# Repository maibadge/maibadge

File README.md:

# MaiBadge

MaiBadge PCB designs, artwork, and firmware.

The maintained CircuitPython firmware for both the bear-shaped and
machine-shaped PCBs is in
[`code/circuitpython-full-slop-port`](code/circuitpython-full-slop-port).
Choose `bear_v1` or `machine_v2` in that directory's `settings.toml` before
uploading. See the
[`manual upload guide`](code/circuitpython-full-slop-port/MANUAL_UPLOAD.md) for
complete installation instructions.

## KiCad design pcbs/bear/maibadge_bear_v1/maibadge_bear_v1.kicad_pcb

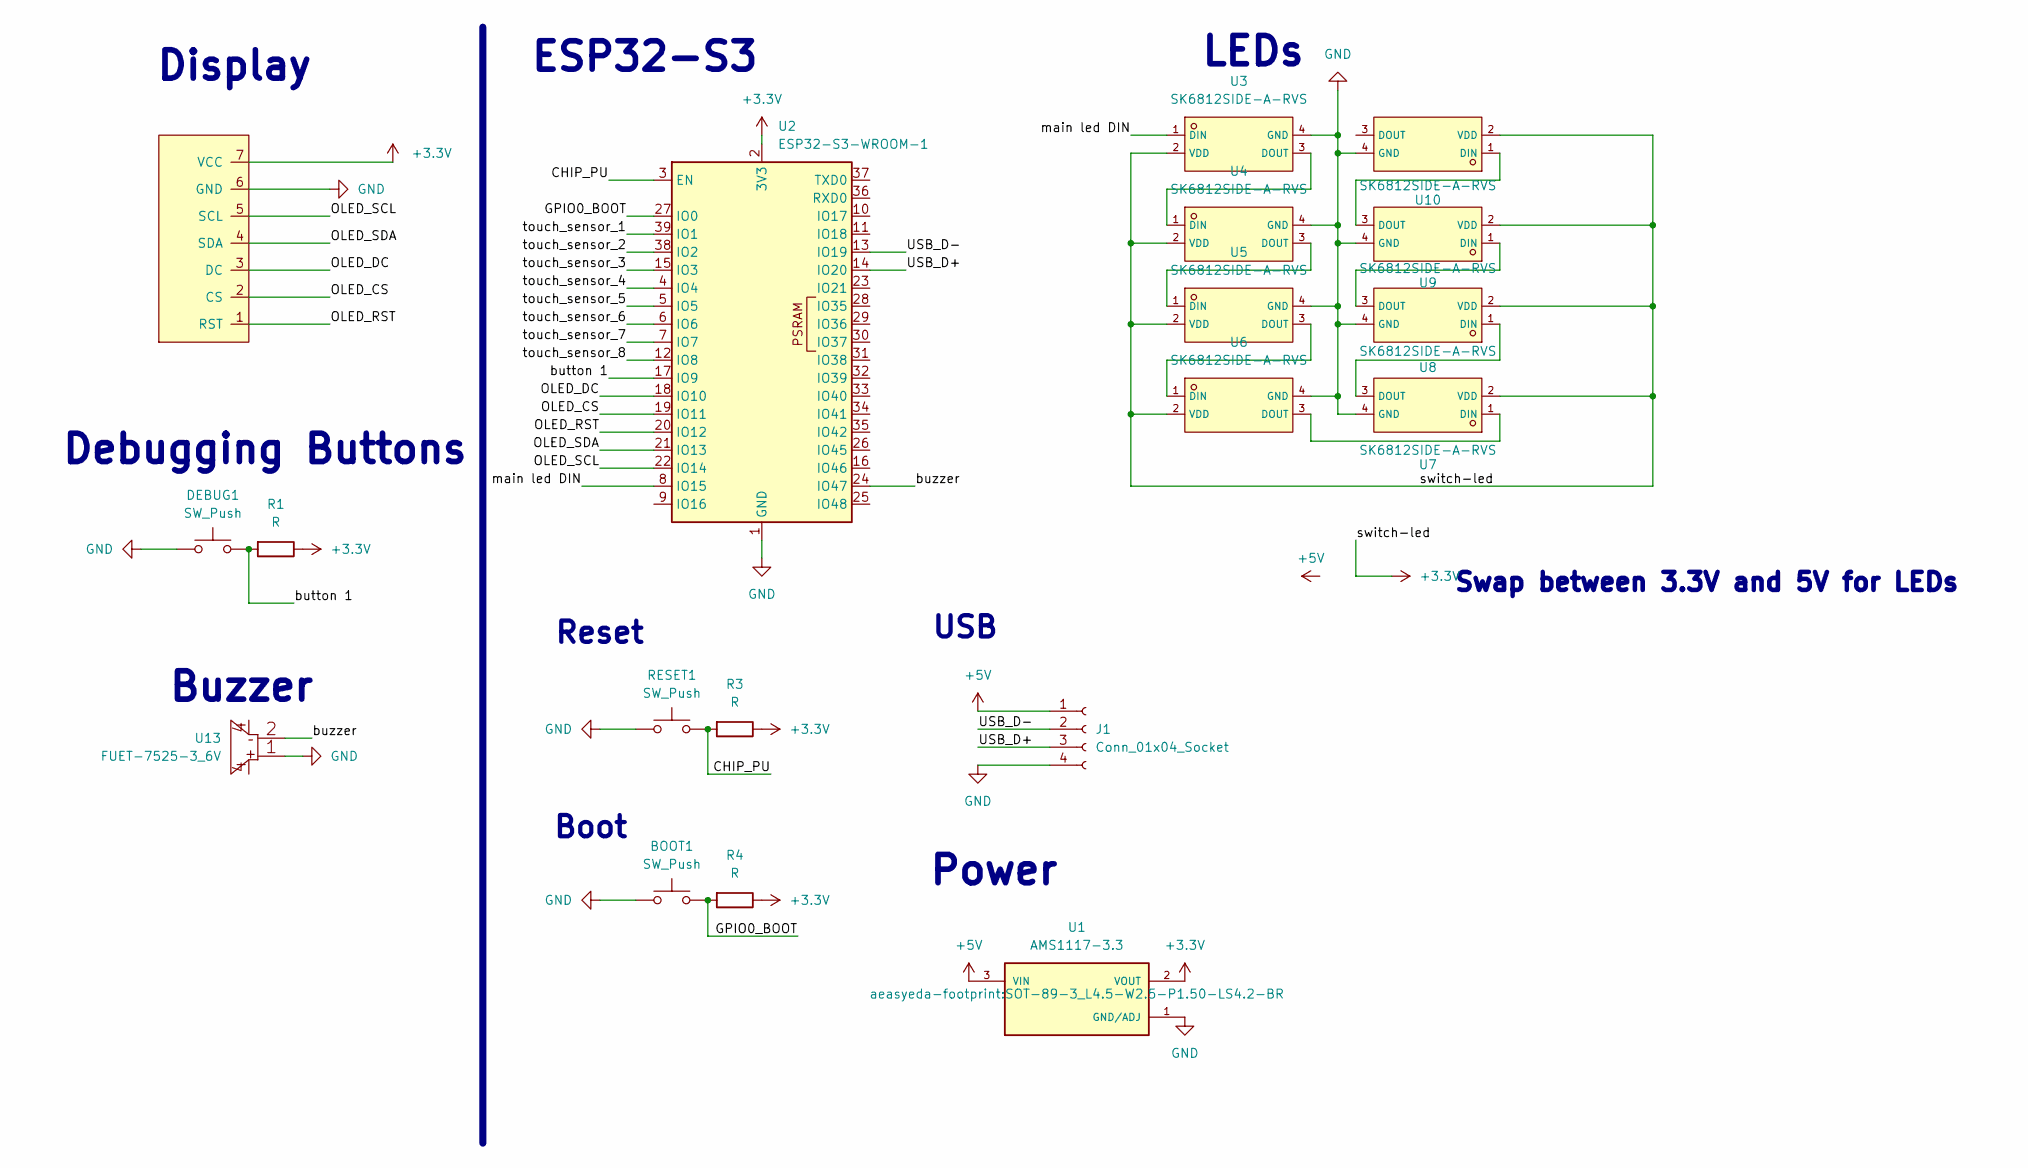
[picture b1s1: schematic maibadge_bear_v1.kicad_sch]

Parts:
BOOT1: SW_Push; SW_Push_1P1T_XKB_TS-1187A
DEBUG1: SW_Push; SW_Push_1P1T_XKB_TS-1187A
GC9A1: CG9A01; GC9A01
J1: Conn_01x04_Socket; PinHeader_1x04_P2.54mm_Vertical
R1, R3, R4: R; R_0805_2012Metric_Pad1.20x1.40mm_HandSolder
RESET1: SW_Push; SW_Push_1P1T_XKB_TS-1187A
U1: AMS1117-3.3; SOT-89-3_L4.5-W2.5-P1.50-LS4.2-BR; PARTREV N/A
U2: ESP32-S3-WROOM-1
U3, U4, U5, U6, U7, U8, U9, U10: SK6812SIDE-A-RVS; LED-SMD_4P-L4.0-W1.6-L; LCSC C2890037
U13: FUET-7525-3_6V; BUZ-SMD_4P-L7.5-W7.5-BR; LCSC C417427

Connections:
+3.3V: GC9A1.7 (VCC), R1.1, R3.1, R4.1, U1.2 (VOUT), U2.2 (3V3), U3.2 (VDD), U4.2 (VDD), U5.2 (VDD), U6.2 (VDD), U7.2 (VDD), U8.2 (VDD), U9.2 (VDD), U10.2 (VDD)
+5V: J1.1, U1.3 (VIN)
/CHIP_PU: R3.2, RESET1.2, U2.3 (EN)
/GPIO0_BOOT: BOOT1.2, R4.2, U2.27 (IO0)
/OLED_CS: GC9A1.2 (CS), U2.19 (IO11)
/OLED_DC: GC9A1.3 (DC), U2.18 (IO10)
/OLED_RST: GC9A1.1 (RST), U2.20 (IO12)
/OLED_SCL: GC9A1.5 (SCL), U2.22 (IO14)
/OLED_SDA: GC9A1.4 (SDA), U2.21 (IO13)
/USB_D+: J1.3, U2.14 (IO20)
/USB_D-: J1.2, U2.13 (IO19)
/button 1: DEBUG1.2, R1.2, U2.17 (IO9)
/buzzer: U2.24 (IO47), U13.2
/main led DIN: U2.8 (IO15), U3.1 (DIN)
/touch_sensor_1: U2.39 (IO1)
/touch_sensor_2: U2.38 (IO2)
/touch_sensor_3: U2.15 (IO3)
/touch_sensor_4: U2.4 (IO4)
/touch_sensor_5: U2.5 (IO5)
/touch_sensor_6: U2.6 (IO6)
/touch_sensor_7: U2.7 (IO7)
/touch_sensor_8: U2.12 (IO8)
GND: BOOT1.1, DEBUG1.1, GC9A1.6 (GND), J1.4, RESET1.1, U1.1 (GND/ADJ), U2.1 (GND), U2.40 (GND), U2.41 (GND), U3.4 (GND), U4.4 (GND), U5.4 (GND), U6.4 (GND), U7.4 (GND), U8.4 (GND), U9.4 (GND), U10.4 (GND), U13.1
unnamed: U3.3 (DOUT), U4.1 (DIN)
unnamed: U4.3 (DOUT), U5.1 (DIN)
unnamed: U5.3 (DOUT), U6.1 (DIN)
unnamed: U6.3 (DOUT), U7.1 (DIN)
unnamed: U7.3 (DOUT), U8.1 (DIN)
unnamed: U8.3 (DOUT), U9.1 (DIN)
unnamed: U9.3 (DOUT), U10.1 (DIN)

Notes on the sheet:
Buzzer
USB
Reset
Swap between 3.3V and 5V for LEDs
Boot
LEDs
Display
Debugging Buttons
ESP32-S3
Power

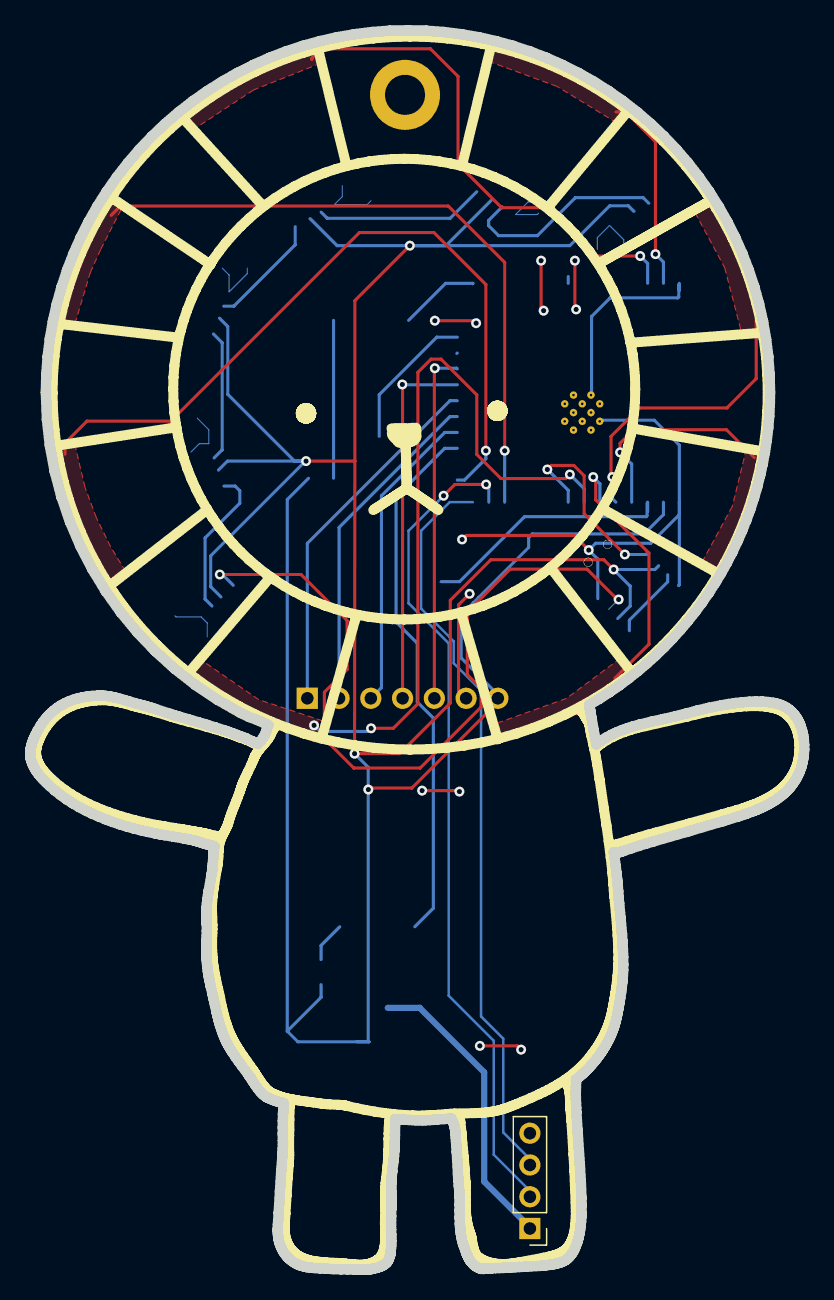
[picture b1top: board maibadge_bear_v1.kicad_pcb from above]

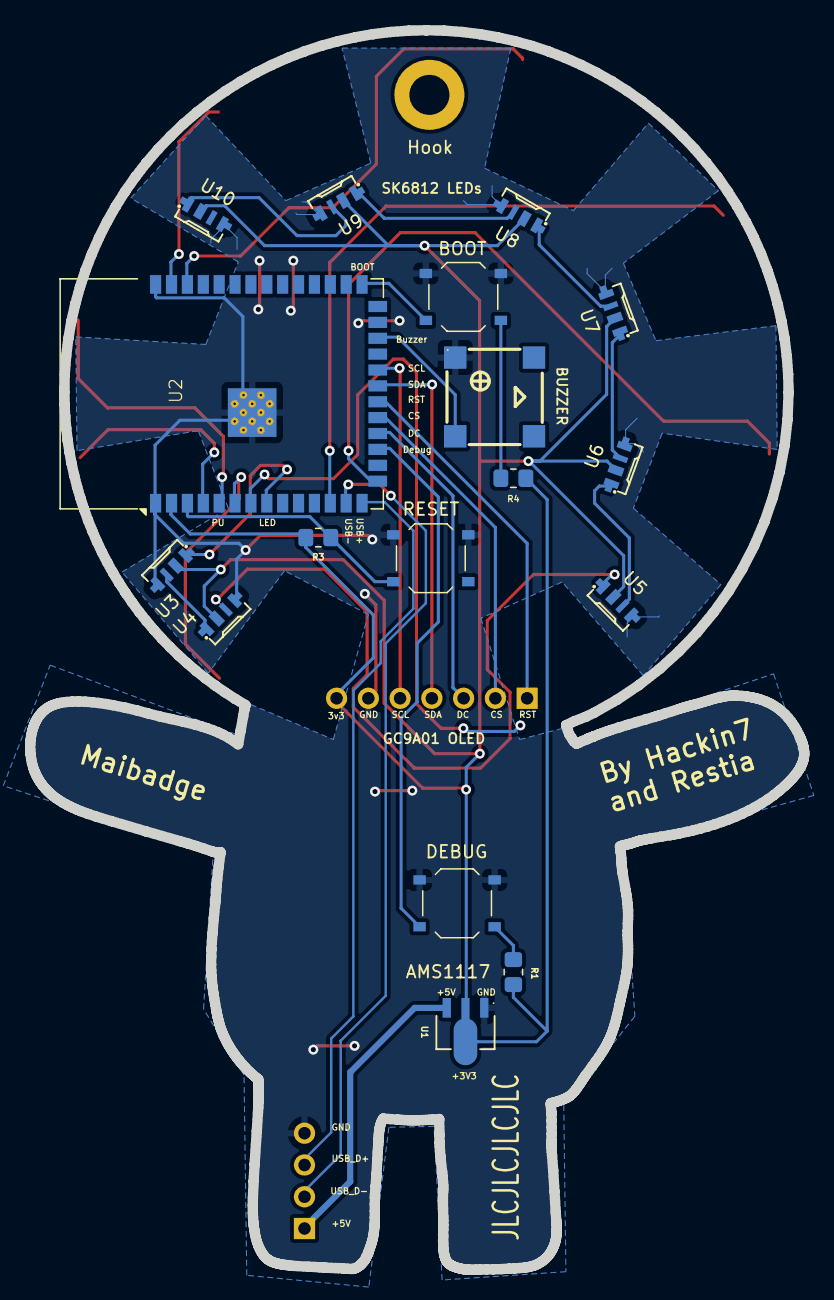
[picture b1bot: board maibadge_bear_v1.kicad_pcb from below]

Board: 2 copper layers, 61.9 x 99.1 mm, 20 parts (18 on the bottom side), 22 nets.

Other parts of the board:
Hook: MountingHole_3.2mm_M3_DIN965_Pad

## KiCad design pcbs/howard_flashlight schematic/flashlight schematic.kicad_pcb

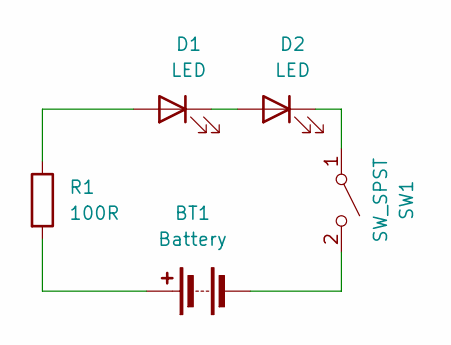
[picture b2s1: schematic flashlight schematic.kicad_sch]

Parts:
BT1: Battery; BatteryHolder_Keystone_106_1x20mm
D1, D2: LED; LED_D1.8mm_W1.8mm_H2.4mm_Horizontal_O1.27mm_Z1.6mm
R1: 100R; R_0201_0603Metric
SW1: SW_SPST; SW_DIP_SPSTx01_Slide_6.7x4.1mm_W6.73mm_P2.54mm_LowProfile_J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

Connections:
unnamed: BT1.1 (+), R1.2
unnamed: BT1.2 (-), SW1.2 (B)
unnamed: D1.2 (A), R1.1
unnamed: D1.1 (K), D2.2 (A)
unnamed: D2.1 (K), SW1.1 (A)

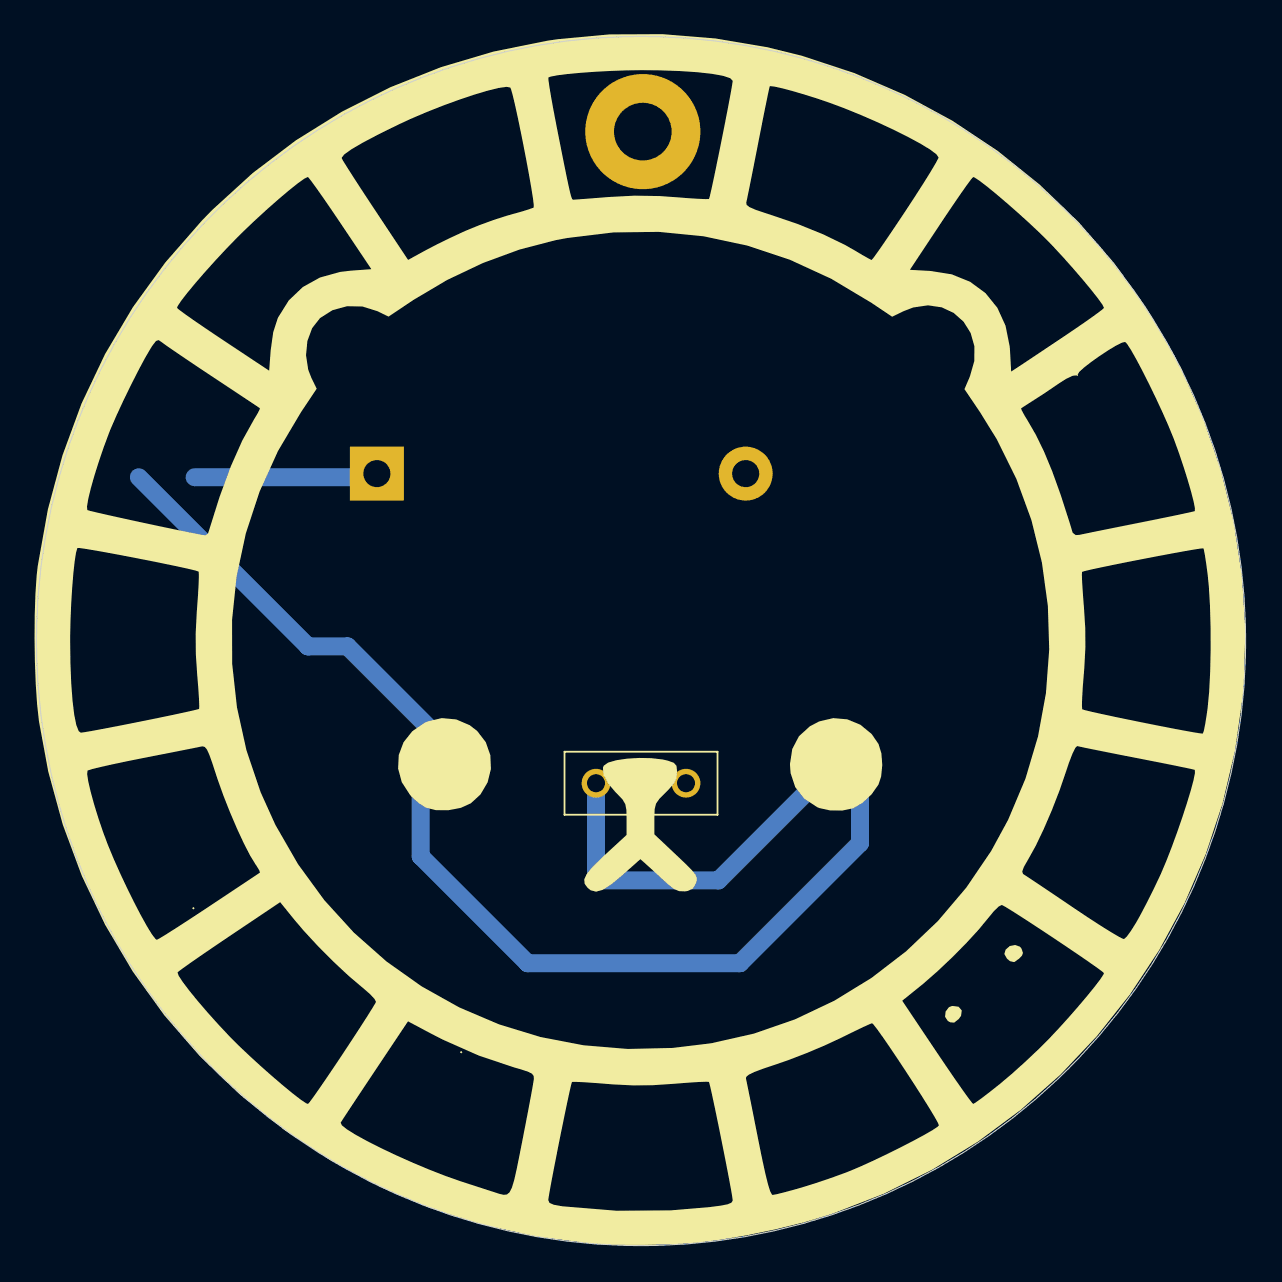
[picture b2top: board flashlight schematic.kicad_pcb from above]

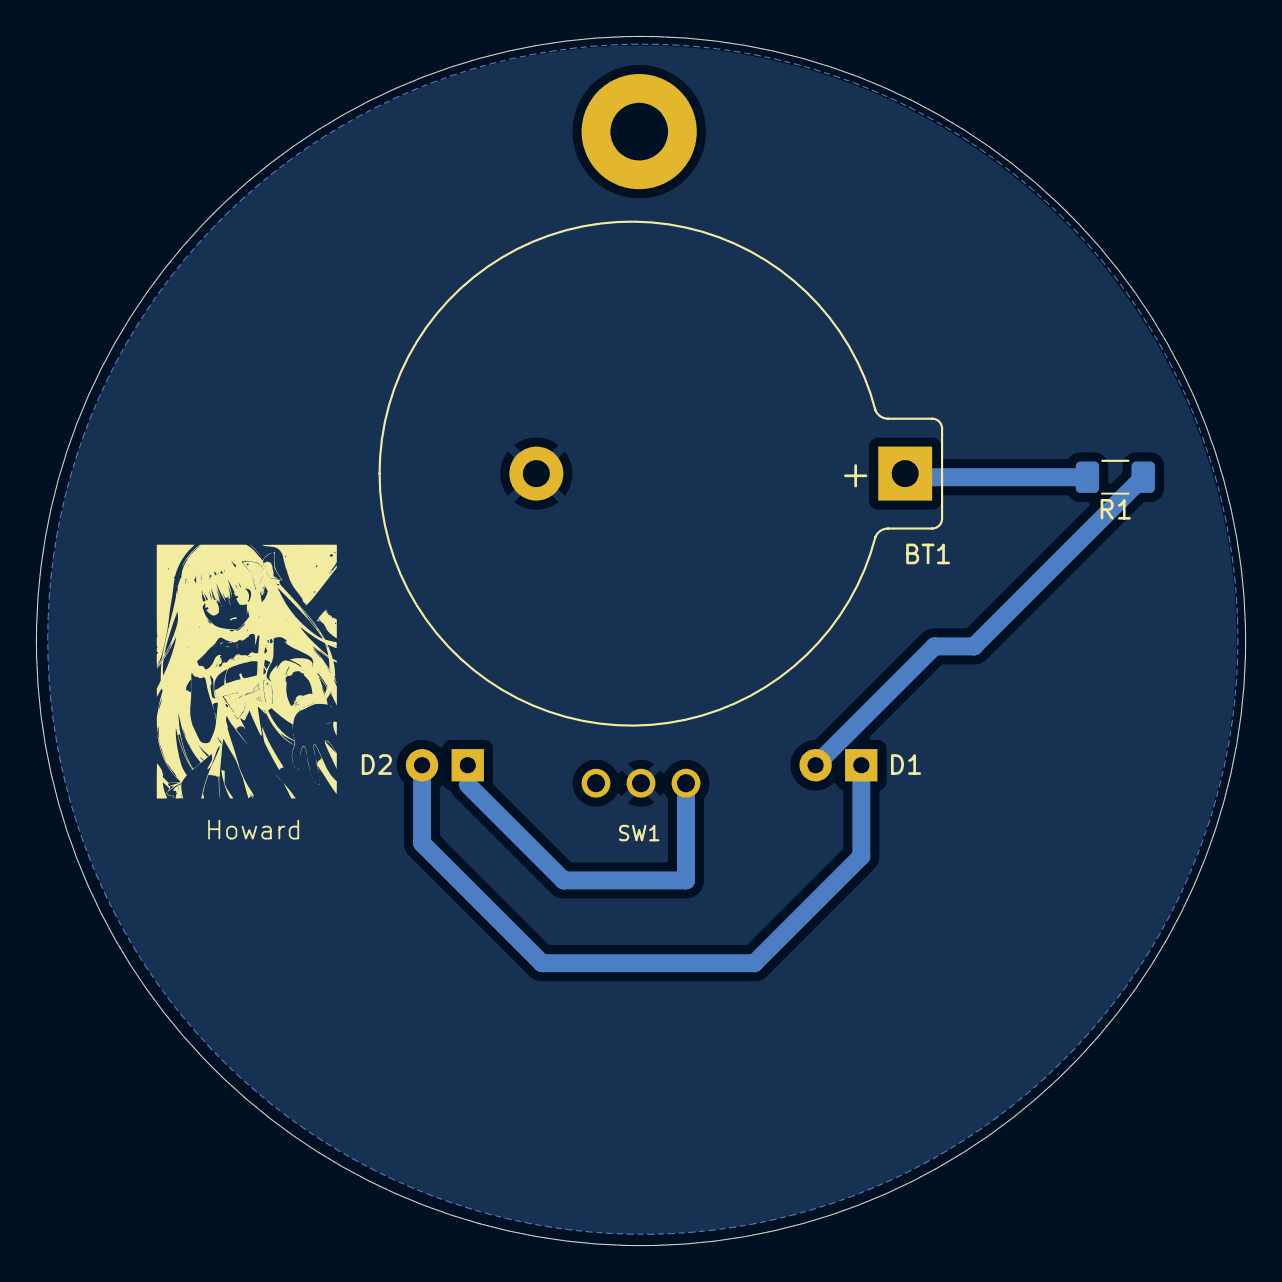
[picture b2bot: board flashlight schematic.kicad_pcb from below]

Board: 2 copper layers, 67.2 x 67.2 mm, 5 parts (2 on the bottom side), 5 nets.

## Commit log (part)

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2025-08-26 circuitpython version
2025-08-26 circuitpython animation
